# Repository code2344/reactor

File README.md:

# helios-core

Helios is a control system for a RBMK style reactor. It can be run as a standalone simulation, or as a server, and I'm making a model

## Install
[ PIPX INSTALL IS STILL ENTIRELY BROKEN, GIT CLONE THE REPO AND RUN PIPX INSTALL . ]
```bash
pipx install helios-core
```
or
```bash
pip install helios-core
```

## Commands

```bash
helios-core                 # Launch GUI
helios-core gui             # Launch GUI
helios-core --server=http://127.0.0.1:8000   # GUI with backend server
helios-core tui             # Launch Textual TUI
helios-core tui --server=http://127.0.0.1:8000
helios-core serve           # Run server only (no GUI)
helios-core serve --port 8000
helios-core map             # Print reactor core map
helios-core stats           # Show rod counts and utilization
helios-core rod-types       # List rod type codes
helios-core estimate 100    # Estimate thermal/electrical output
helios-core guide           # Show packaged operator guide path
helios-core guide --print   # Print operator guide text
```

## Backward compatibility

The original launcher script remains available:

```bash
python main.py
python channel-deviation-view.py
```

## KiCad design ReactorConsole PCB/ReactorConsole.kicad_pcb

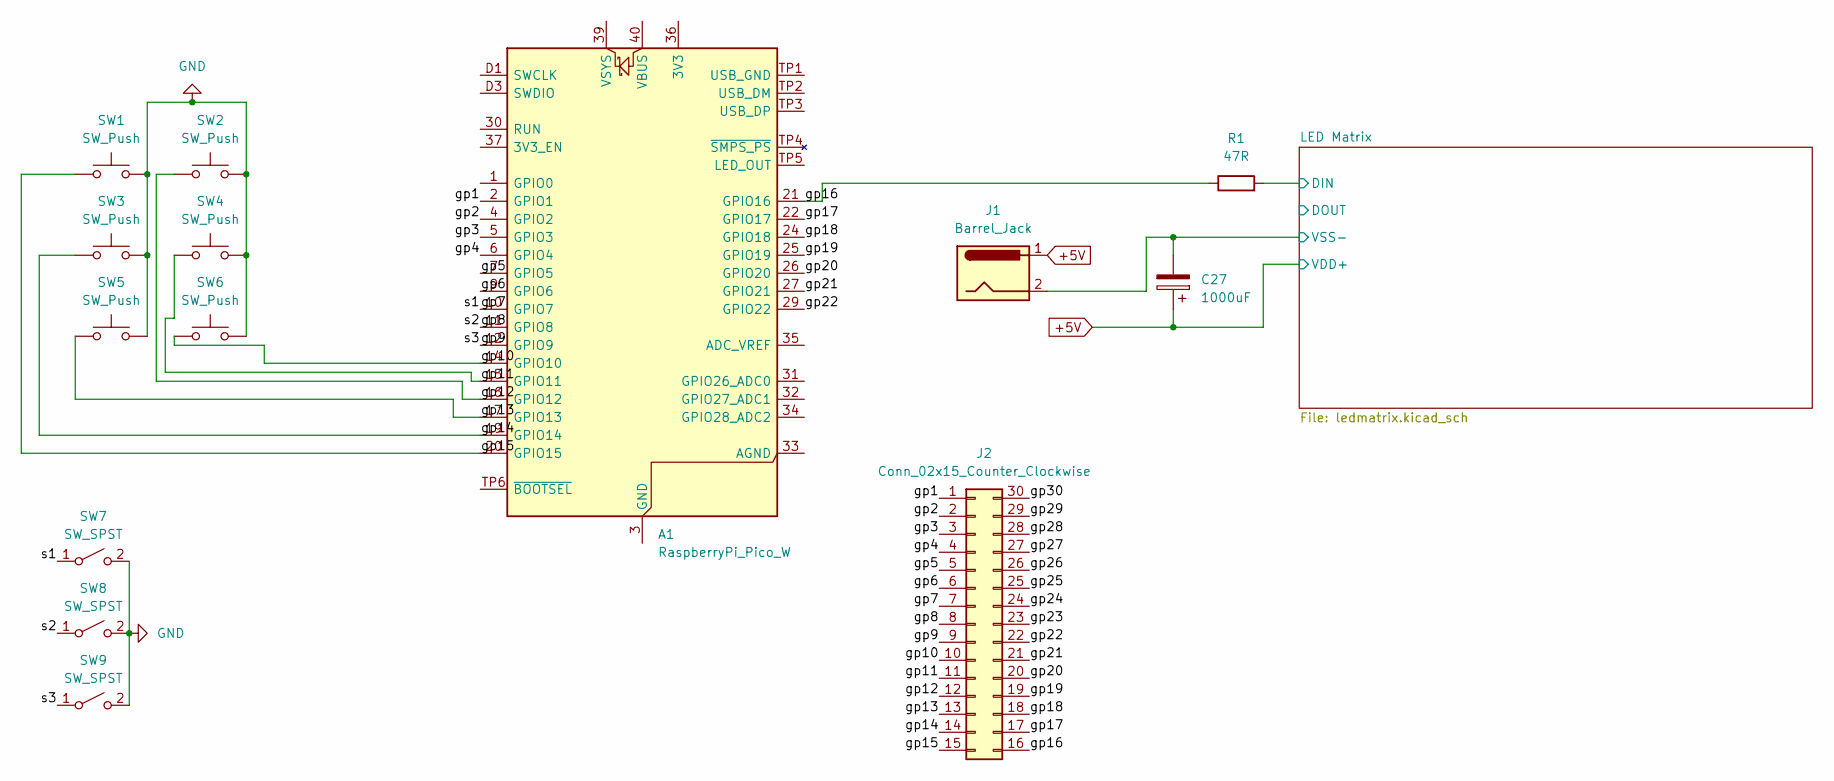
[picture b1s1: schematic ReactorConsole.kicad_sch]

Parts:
A1: RaspberryPi_Pico_W; RaspberryPi_Pico_W_SMD
C27: 1000uF; CP_Radial_D10.0mm_P5.00mm
J1: Barrel_Jack; BarrelJack_SwitchcraftConxall_RAPC10U_Horizontal
J2: Conn_02x15_Counter_Clockwise; PinHeader_2x15_P1.00mm_Horizontal
R1: 47R; R_0603_1608Metric
SW1, SW2, SW3, SW4, SW5, SW6: SW_Push; SW_Push_1P1T_NO_CK_KMR2
SW7, SW8, SW9: SW_SPST; SW_DIP_SPSTx01_Slide_6.7x4.1mm_W6.73mm_P2.54mm_LowProfile_J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

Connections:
+5V: C27.1, J1.1; also elsewhere on the board
/LED Matrix/DIN: R1.2; also elsewhere on the board
/LED Matrix/VSS-: C27.2, J1.2; also elsewhere on the board
/gp1: A1.2 (GPIO1), J2.1
/gp2: A1.4 (GPIO2), J2.2
/gp3: A1.5 (GPIO3), J2.3
/gp4: A1.6 (GPIO4), J2.4
/gp5: A1.7 (GPIO5), J2.5
/gp6: A1.9 (GPIO6), J2.6
/gp7: A1.10 (GPIO7), J2.7, SW7.1 (A)
/gp8: A1.11 (GPIO8), J2.8, SW8.1 (A)
/gp9: A1.12 (GPIO9), J2.9, SW9.1 (A)
/gp10: A1.14 (GPIO10), J2.10, SW6.1
/gp11: A1.15 (GPIO11), J2.11, SW4.1
/gp12: A1.16 (GPIO12), J2.12, SW2.1
/gp13: A1.17 (GPIO13), J2.13, SW5.1
/gp14: A1.19 (GPIO14), J2.14, SW3.1
/gp15: A1.20 (GPIO15), J2.15, SW1.1
/gp16: A1.21 (GPIO16), J2.16, R1.1
/gp17: A1.22 (GPIO17), J2.17
/gp18: A1.24 (GPIO18), J2.18
/gp19: A1.25 (GPIO19), J2.19
/gp20: A1.26 (GPIO20), J2.20
/gp21: A1.27 (GPIO21), J2.21
/gp22: A1.29 (GPIO22), J2.22
/gp23: J2.23
/gp24: J2.24
/gp25: J2.25
/gp26: J2.26
/gp27: J2.27
/gp28: J2.28
/gp29: J2.29
/gp30: J2.30
GND: SW1.2, SW2.2, SW3.2, SW4.2, SW5.2, SW6.2, SW7.2 (B), SW8.2 (B), SW9.2 (B)
unnamed: A1.3 (GND), A1.8 (GND), A1.13 (GND), A1.18 (GND), A1.23 (GND), A1.28 (GND), A1.38 (GND), A1.D2 (GND)

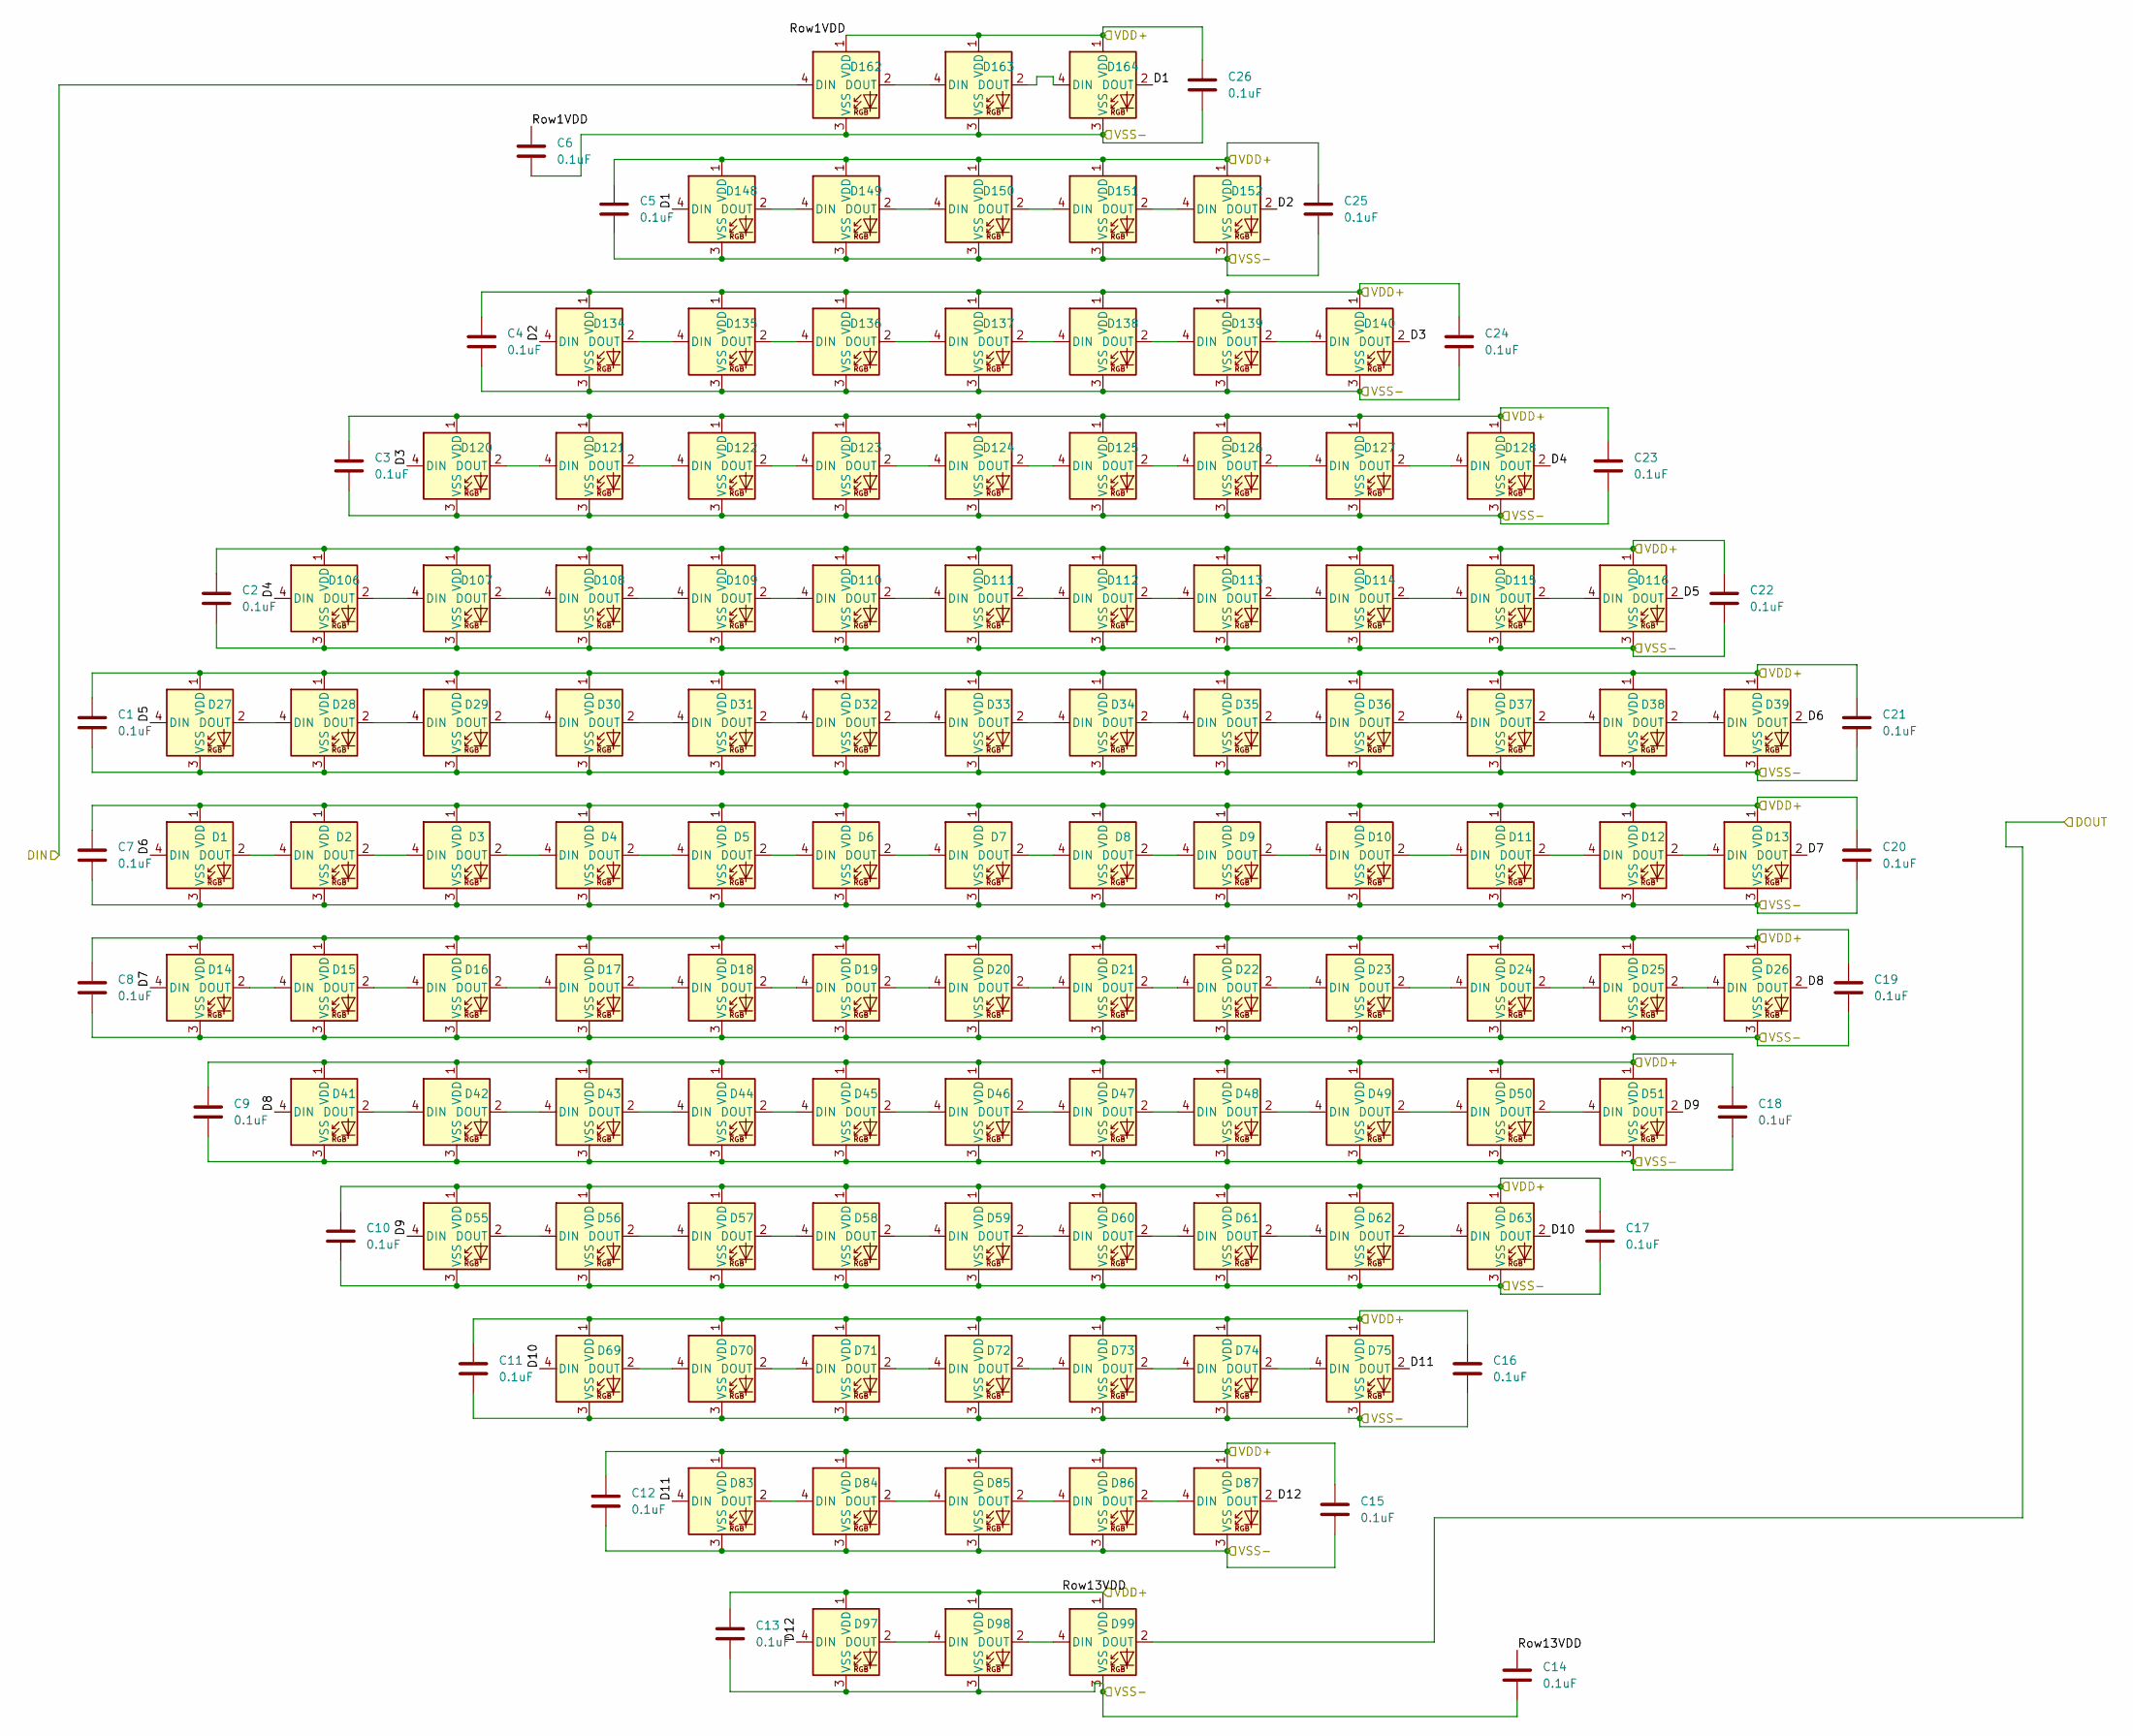
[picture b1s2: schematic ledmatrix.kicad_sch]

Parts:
C1, C2, C3, C4, C5, C6, C7, C8, C9, C10, C11, C12, C13, C14, C15, C16, C17, C18, C19, C20, C21, C22, C23, C24, C25, C26: 0.1uF; C_0603_1608Metric
D1, D2, D3, D4, D5, D6, D7, D8, D9, D10, D11, D12, D13, D14, D15, D16, D17, D18, D19, D20, D21, D22, D23, D24, D25, D26, D27, D28, D29, D30, D31, D32, D33, D34, D35, D36, D37, D38, D39, D41, D42, D43, D44, D45, D46, D47, D48, D49, D50, D51, D55, D56, D57, D58, D59, D60, D61, D62, D63, D69, D70, D71, D72, D73, D74, D75, D83, D84, D85, D86, D87, D97, D98, D99, D106, D107, D108, D109, D110, D111, D112, D113, D114, D115, D116, D120, D121, D122, D123, D124, D125, D126, D127, D128, D134, D135, D136, D137, D138, D139, D140, D148, D149, D150, D151, D152, D162, D163, D164: LED_SK6812_PLCC4_5.0x5.0mm_P3.2mm

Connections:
+5V: C1.1, C2.1, C3.1, C4.1, C5.1, C6.1, C7.1, C8.1, C9.1, C10.1, C11.1, C12.1, C13.1, C14.1, C15.1, C16.1, C17.1, C18.1, C19.1, C20.1, C21.1, C22.1, C23.1, C24.1, C25.1, C26.1, D1.1 (VDD), D2.1 (VDD), D3.1 (VDD), D4.1 (VDD), D5.1 (VDD), D6.1 (VDD), D7.1 (VDD), D8.1 (VDD), D9.1 (VDD), D10.1 (VDD), D11.1 (VDD), D12.1 (VDD), D13.1 (VDD), D14.1 (VDD), D15.1 (VDD), D16.1 (VDD), D17.1 (VDD), D18.1 (VDD), D19.1 (VDD), D20.1 (VDD), D21.1 (VDD), D22.1 (VDD), D23.1 (VDD), D24.1 (VDD), D25.1 (VDD), D26.1 (VDD), D27.1 (VDD), D28.1 (VDD), D29.1 (VDD), D30.1 (VDD), D31.1 (VDD), D32.1 (VDD), D33.1 (VDD), D34.1 (VDD), D35.1 (VDD), D36.1 (VDD), D37.1 (VDD), D38.1 (VDD), D39.1 (VDD), D41.1 (VDD), D42.1 (VDD), D43.1 (VDD), D44.1 (VDD), D45.1 (VDD), D46.1 (VDD), D47.1 (VDD), D48.1 (VDD), D49.1 (VDD), D50.1 (VDD), D51.1 (VDD), D55.1 (VDD), D56.1 (VDD), D57.1 (VDD), D58.1 (VDD), D59.1 (VDD), D60.1 (VDD), D61.1 (VDD), D62.1 (VDD), D63.1 (VDD), D69.1 (VDD), D70.1 (VDD), D71.1 (VDD), D72.1 (VDD), D73.1 (VDD), D74.1 (VDD), D75.1 (VDD), D83.1 (VDD), D84.1 (VDD), D85.1 (VDD), D86.1 (VDD), D87.1 (VDD), D97.1 (VDD), D98.1 (VDD), D99.1 (VDD), D106.1 (VDD), D107.1 (VDD), D108.1 (VDD), D109.1 (VDD), D110.1 (VDD), D111.1 (VDD), D112.1 (VDD), D113.1 (VDD), D114.1 (VDD), D115.1 (VDD), D116.1 (VDD), D120.1 (VDD), D121.1 (VDD), D122.1 (VDD), D123.1 (VDD), D124.1 (VDD), D125.1 (VDD), D126.1 (VDD), D127.1 (VDD), D128.1 (VDD), D134.1 (VDD), D135.1 (VDD), D136.1 (VDD), D137.1 (VDD), D138.1 (VDD), D139.1 (VDD), D140.1 (VDD), D148.1 (VDD), D149.1 (VDD), D150.1 (VDD), D151.1 (VDD), D152.1 (VDD), D162.1 (VDD), D163.1 (VDD), D164.1 (VDD); also elsewhere on the board
/LED Matrix/D1: D148.4 (DIN), D164.2 (DOUT)
/LED Matrix/D2: D134.4 (DIN), D152.2 (DOUT)
/LED Matrix/D3: D120.4 (DIN), D140.2 (DOUT)
/LED Matrix/D4: D106.4 (DIN), D128.2 (DOUT)
/LED Matrix/D5: D27.4 (DIN), D116.2 (DOUT)
/LED Matrix/D6: D1.4 (DIN), D39.2 (DOUT)
/LED Matrix/D7: D13.2 (DOUT), D14.4 (DIN)
/LED Matrix/D8: D26.2 (DOUT), D41.4 (DIN)
/LED Matrix/D9: D51.2 (DOUT), D55.4 (DIN)
/LED Matrix/D10: D63.2 (DOUT), D69.4 (DIN)
/LED Matrix/D11: D75.2 (DOUT), D83.4 (DIN)
/LED Matrix/D12: D87.2 (DOUT), D97.4 (DIN)
/LED Matrix/DIN: D162.4 (DIN); also elsewhere on the board
/LED Matrix/DOUT: D99.2 (DOUT)
/LED Matrix/VSS-: C1.2, C2.2, C3.2, C4.2, C5.2, C6.2, C7.2, C8.2, C9.2, C10.2, C11.2, C12.2, C13.2, C14.2, C15.2, C16.2, C17.2, C18.2, C19.2, C20.2, C21.2, C22.2, C23.2, C24.2, C25.2, C26.2, D1.3 (VSS), D2.3 (VSS), D3.3 (VSS), D4.3 (VSS), D5.3 (VSS), D6.3 (VSS), D7.3 (VSS), D8.3 (VSS), D9.3 (VSS), D10.3 (VSS), D11.3 (VSS), D12.3 (VSS), D13.3 (VSS), D14.3 (VSS), D15.3 (VSS), D16.3 (VSS), D17.3 (VSS), D18.3 (VSS), D19.3 (VSS), D20.3 (VSS), D21.3 (VSS), D22.3 (VSS), D23.3 (VSS), D24.3 (VSS), D25.3 (VSS), D26.3 (VSS), D27.3 (VSS), D28.3 (VSS), D29.3 (VSS), D30.3 (VSS), D31.3 (VSS), D32.3 (VSS), D33.3 (VSS), D34.3 (VSS), D35.3 (VSS), D36.3 (VSS), D37.3 (VSS), D38.3 (VSS), D39.3 (VSS), D41.3 (VSS), D42.3 (VSS), D43.3 (VSS), D44.3 (VSS), D45.3 (VSS), D46.3 (VSS), D47.3 (VSS), D48.3 (VSS), D49.3 (VSS), D50.3 (VSS), D51.3 (VSS), D55.3 (VSS), D56.3 (VSS), D57.3 (VSS), D58.3 (VSS), D59.3 (VSS), D60.3 (VSS), D61.3 (VSS), D62.3 (VSS), D63.3 (VSS), D69.3 (VSS), D70.3 (VSS), D71.3 (VSS), D72.3 (VSS), D73.3 (VSS), D74.3 (VSS), D75.3 (VSS), D83.3 (VSS), D84.3 (VSS), D85.3 (VSS), D86.3 (VSS), D87.3 (VSS), D97.3 (VSS), D98.3 (VSS), D99.3 (VSS), D106.3 (VSS), D107.3 (VSS), D108.3 (VSS), D109.3 (VSS), D110.3 (VSS), D111.3 (VSS), D112.3 (VSS), D113.3 (VSS), D114.3 (VSS), D115.3 (VSS), D116.3 (VSS), D120.3 (VSS), D121.3 (VSS), D122.3 (VSS), D123.3 (VSS), D124.3 (VSS), D125.3 (VSS), D126.3 (VSS), D127.3 (VSS), D128.3 (VSS), D134.3 (VSS), D135.3 (VSS), D136.3 (VSS), D137.3 (VSS), D138.3 (VSS), D139.3 (VSS), D140.3 (VSS), D148.3 (VSS), D149.3 (VSS), D150.3 (VSS), D151.3 (VSS), D152.3 (VSS), D162.3 (VSS), D163.3 (VSS), D164.3 (VSS); also elsewhere on the board
unnamed: D1.2 (DOUT), D2.4 (DIN)
unnamed: D2.2 (DOUT), D3.4 (DIN)
unnamed: D3.2 (DOUT), D4.4 (DIN)
unnamed: D4.2 (DOUT), D5.4 (DIN)
unnamed: D5.2 (DOUT), D6.4 (DIN)
unnamed: D6.2 (DOUT), D7.4 (DIN)
unnamed: D7.2 (DOUT), D8.4 (DIN)
unnamed: D8.2 (DOUT), D9.4 (DIN)
unnamed: D9.2 (DOUT), D10.4 (DIN)
unnamed: D10.2 (DOUT), D11.4 (DIN)
unnamed: D11.2 (DOUT), D12.4 (DIN)
unnamed: D12.2 (DOUT), D13.4 (DIN)
unnamed: D14.2 (DOUT), D15.4 (DIN)
unnamed: D15.2 (DOUT), D16.4 (DIN)
unnamed: D16.2 (DOUT), D17.4 (DIN)
unnamed: D17.2 (DOUT), D18.4 (DIN)
unnamed: D18.2 (DOUT), D19.4 (DIN)
unnamed: D19.2 (DOUT), D20.4 (DIN)
unnamed: D20.2 (DOUT), D21.4 (DIN)
unnamed: D21.2 (DOUT), D22.4 (DIN)
unnamed: D22.2 (DOUT), D23.4 (DIN)
unnamed: D23.2 (DOUT), D24.4 (DIN)
unnamed: D24.2 (DOUT), D25.4 (DIN)
unnamed: D25.2 (DOUT), D26.4 (DIN)
unnamed: D27.2 (DOUT), D28.4 (DIN)
unnamed: D28.2 (DOUT), D29.4 (DIN)
unnamed: D29.2 (DOUT), D30.4 (DIN)
unnamed: D30.2 (DOUT), D31.4 (DIN)
unnamed: D31.2 (DOUT), D32.4 (DIN)
unnamed: D32.2 (DOUT), D33.4 (DIN)
unnamed: D33.2 (DOUT), D34.4 (DIN)
unnamed: D34.2 (DOUT), D35.4 (DIN)
unnamed: D35.2 (DOUT), D36.4 (DIN)
unnamed: D36.2 (DOUT), D37.4 (DIN)
unnamed: D37.2 (DOUT), D38.4 (DIN)
unnamed: D38.2 (DOUT), D39.4 (DIN)
unnamed: D41.2 (DOUT), D42.4 (DIN)
unnamed: D42.2 (DOUT), D43.4 (DIN)
unnamed: D43.2 (DOUT), D44.4 (DIN)
unnamed: D44.2 (DOUT), D45.4 (DIN)
unnamed: D45.2 (DOUT), D46.4 (DIN)
unnamed: D46.2 (DOUT), D47.4 (DIN)
unnamed: D47.2 (DOUT), D48.4 (DIN)
unnamed: D48.2 (DOUT), D49.4 (DIN)
unnamed: D49.2 (DOUT), D50.4 (DIN)
unnamed: D50.2 (DOUT), D51.4 (DIN)
unnamed: D55.2 (DOUT), D56.4 (DIN)
unnamed: D56.2 (DOUT), D57.4 (DIN)
unnamed: D57.2 (DOUT), D58.4 (DIN)
unnamed: D58.2 (DOUT), D59.4 (DIN)
unnamed: D59.2 (DOUT), D60.4 (DIN)
unnamed: D60.2 (DOUT), D61.4 (DIN)
unnamed: D61.2 (DOUT), D62.4 (DIN)
unnamed: D62.2 (DOUT), D63.4 (DIN)
unnamed: D69.2 (DOUT), D70.4 (DIN)
unnamed: D70.2 (DOUT), D71.4 (DIN)
unnamed: D71.2 (DOUT), D72.4 (DIN)
unnamed: D72.2 (DOUT), D73.4 (DIN)
unnamed: D73.2 (DOUT), D74.4 (DIN)
unnamed: D74.2 (DOUT), D75.4 (DIN)
unnamed: D83.2 (DOUT), D84.4 (DIN)
unnamed: D84.2 (DOUT), D85.4 (DIN)
unnamed: D85.2 (DOUT), D86.4 (DIN)
unnamed: D86.2 (DOUT), D87.4 (DIN)
unnamed: D97.2 (DOUT), D98.4 (DIN)
unnamed: D98.2 (DOUT), D99.4 (DIN)
unnamed: D106.2 (DOUT), D107.4 (DIN)
unnamed: D107.2 (DOUT), D108.4 (DIN)
unnamed: D108.2 (DOUT), D109.4 (DIN)
unnamed: D109.2 (DOUT), D110.4 (DIN)
unnamed: D110.2 (DOUT), D111.4 (DIN)
unnamed: D111.2 (DOUT), D112.4 (DIN)
unnamed: D112.2 (DOUT), D113.4 (DIN)
unnamed: D113.2 (DOUT), D114.4 (DIN)
unnamed: D114.2 (DOUT), D115.4 (DIN)
unnamed: D115.2 (DOUT), D116.4 (DIN)
unnamed: D120.2 (DOUT), D121.4 (DIN)
unnamed: D121.2 (DOUT), D122.4 (DIN)
unnamed: D122.2 (DOUT), D123.4 (DIN)
unnamed: D123.2 (DOUT), D124.4 (DIN)
unnamed: D124.2 (DOUT), D125.4 (DIN)
unnamed: D125.2 (DOUT), D126.4 (DIN)
unnamed: D126.2 (DOUT), D127.4 (DIN)
unnamed: D127.2 (DOUT), D128.4 (DIN)
unnamed: D134.2 (DOUT), D135.4 (DIN)
unnamed: D135.2 (DOUT), D136.4 (DIN)
unnamed: D136.2 (DOUT), D137.4 (DIN)
unnamed: D137.2 (DOUT), D138.4 (DIN)
unnamed: D138.2 (DOUT), D139.4 (DIN)
unnamed: D139.2 (DOUT), D140.4 (DIN)
unnamed: D148.2 (DOUT), D149.4 (DIN)
unnamed: D149.2 (DOUT), D150.4 (DIN)
unnamed: D150.2 (DOUT), D151.4 (DIN)
unnamed: D151.2 (DOUT), D152.4 (DIN)
unnamed: D162.2 (DOUT), D163.4 (DIN)
unnamed: D163.2 (DOUT), D164.4 (DIN)

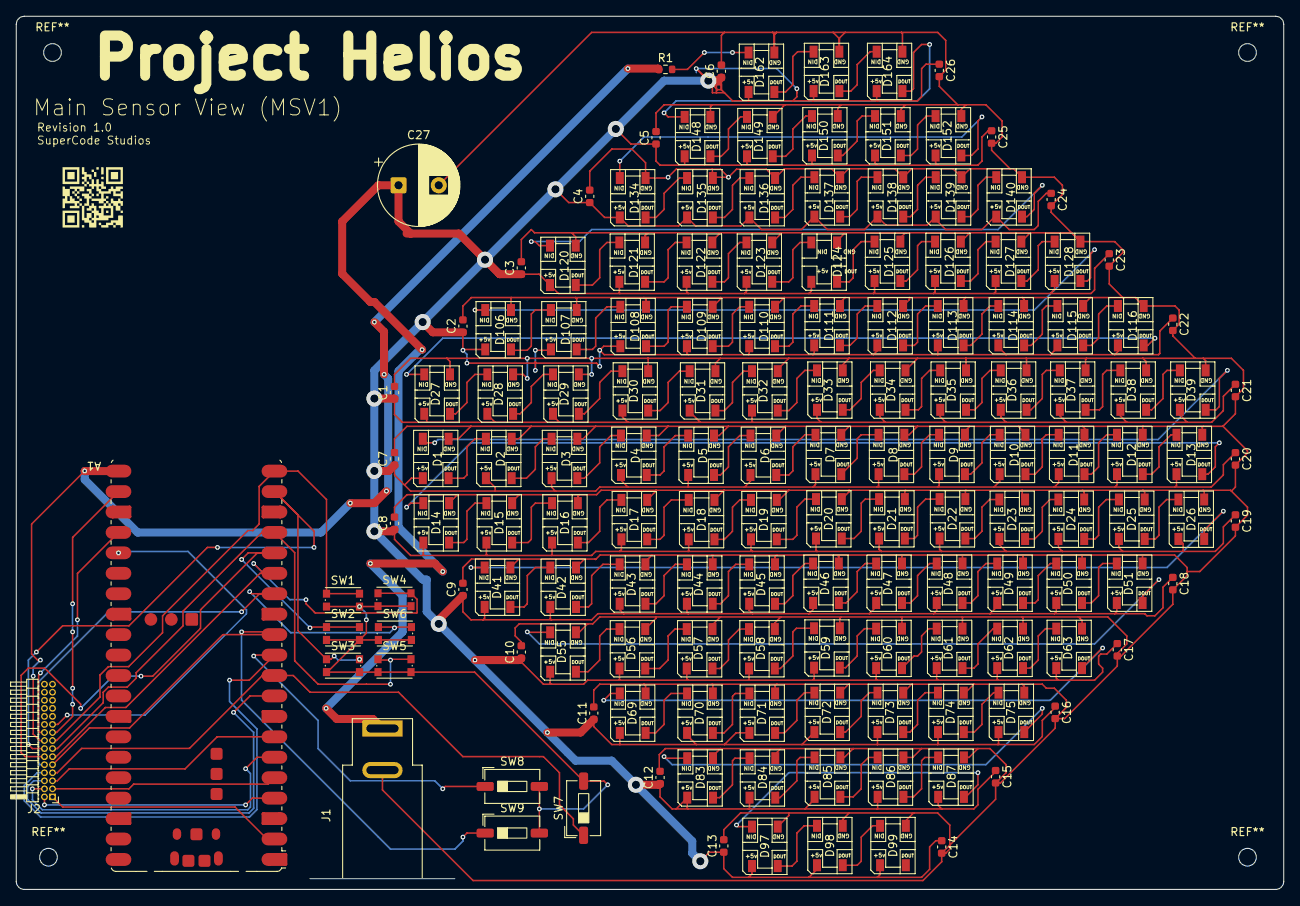
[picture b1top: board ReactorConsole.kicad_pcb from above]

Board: 2 copper layers, 157.5 x 108.5 mm, 150 parts (0 on the bottom side), 135 nets.

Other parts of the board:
QR${REFERENCE}: https://scstudios.tech; httpsscstudios.tech

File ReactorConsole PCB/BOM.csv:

"Id";"Designator";"Footprint";"Quantity";"Designation";"Supplier and ref";
1;"QRQRQR${REFERENCE}";"httpsscstudios.tech";1;"https://scstudios.tech";;;
2;"J2";"PinHeader_2x15_P1.00mm_Horizontal";1;"Conn_02x15_Counter_Clockwise";;;
3;"D36,D38,D5,D148,D3,D114,D25,D26,D115,D56,D4,D139,D63,D150,D42,D48,D60,D99,D58,D71,D152,D1,D111,D16,D123,D18,D98,D70,D84,D55,D11,D19,D97,D2,D137,D62,D43,D37,D164,D35,D109,D116,D151,D69,D17,D127,D34,D13,D14,D121,D113,D138,D85,D39,D75,D112,D126,D31,D73,D51,D87,D44,D106,D21,D29,D72,D163,D107,D86,D7,D22,D140,D125,D23,D27,D108,D59,D149,D32,D124,D61,D128,D33,D8,D9,D122,D12,D41,D83,D15,D57,D30,D28,D20,D10,D74,D120,D6,D47,D45,D24,D49,D135,D50,D162,D110,D46,D136,D134";"LED_SK6812_PLCC4_5.0x5.0mm_P3.2mm";109;"~";;;
4;"C16,C11,C22,C1,C9,C20,C25,C14,C19,C12,C21,C23,C17,C10,C2,C13,C5,C18,C3,C4,C24,C15,C6,C26,C7,C8";"C_0603_1608Metric";26;"0.1uF";;;
5;"SW5,SW6,SW3,SW2,SW4,SW1";"SW_Push_1P1T_NO_CK_KMR2";6;"SW_Push";;;
6;"J1";"BarrelJack_SwitchcraftConxall_RAPC10U_Horizontal";1;"Barrel_Jack";;;
7;"SW8,SW9,SW7";"SW_DIP_SPSTx01_Slide_6.7x4.1mm_W6.73mm_P2.54mm_LowProfile_JPin";3;"SW_SPST";;;
8;"R1";"R_0603_1608Metric";1;"47R";;;
9;"C27";"CP_Radial_D10.0mm_P5.00mm";1;"1000uF";;;
10;"A1";"RaspberryPi_Pico_W_SMD";1;"RaspberryPi_Pico_W";;;

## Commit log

2026-02-16 Add initial implementation of alarm grid UI
2026-02-18 Implement feature X to enhance user experience and fix bug Y in module Z
2026-02-18 Enhance GridUI with ARCCS features, including automated control logic, command staging, and improved temperature management
2026-02-18 Update GridUI temperature handling and add operator guidance manual
2026-02-18 Enhance GridUI with detailed indicator boxes for temperature, pressure, fuel, and neutron flux, and improve ARCCS recommendations and logging
2026-02-18 Enhance operator guide with detailed reactor grid indicators and ARCCS recommendations, and clarify power control instructions
2026-02-18 Enhance operator guide with detailed ARCCS recommendations, intelligent logging features, and realistic operation instructions for power adjustments
2026-02-20 Refactor code structure for improved readability and maintainability
2026-03-03 Add CLI for RBMK reactor control station with various commands
    - Implemented `cli.py` to provide a command-line interface for reactor control.
    - Added subcommands for launching GUI, displaying reactor map, showing statistics, listing rod types, estimating output, and printing operator guide.
    - Introduced `reactor_data.py` to define reactor grid layout and rod types.
    - Created `reactor_utils.py` for utility functions including grid flattening, rod counting, ASCII map rendering, reactor statistics, output estimation, and rod type table generation.
    - Added operator guidance manual in `OPERATOR_GUIDE.txt` detailing reactor operation procedures, command references, and emergency protocols.
2026-03-03 Add HeliosServer and HeliosRequestHandler classes for reactor server functionality
2026-03-03 Add GNU General Public License v3
2026-03-03 Add TUI for Reactor Control and Server Interaction
    - Implemented a Textual User Interface (TUI) in `tui.py` for managing reactor control rods.
    - Created a main entry point in `main.py` to run the TUI application.
    - Added HTTP server tests in `test_server.py` to validate health checks and rod updates.
    - Developed state management tests in `test_state.py` to ensure correct control rod updates and alarm acknowledgment.
    - Introduced a `conftest.py` for test configuration and path management.
2026-04-15 added pcb files
